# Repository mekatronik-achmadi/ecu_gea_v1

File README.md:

ecu_gea_v1
==========

engine controller unit for gea engines. curently input only RPM and TPS

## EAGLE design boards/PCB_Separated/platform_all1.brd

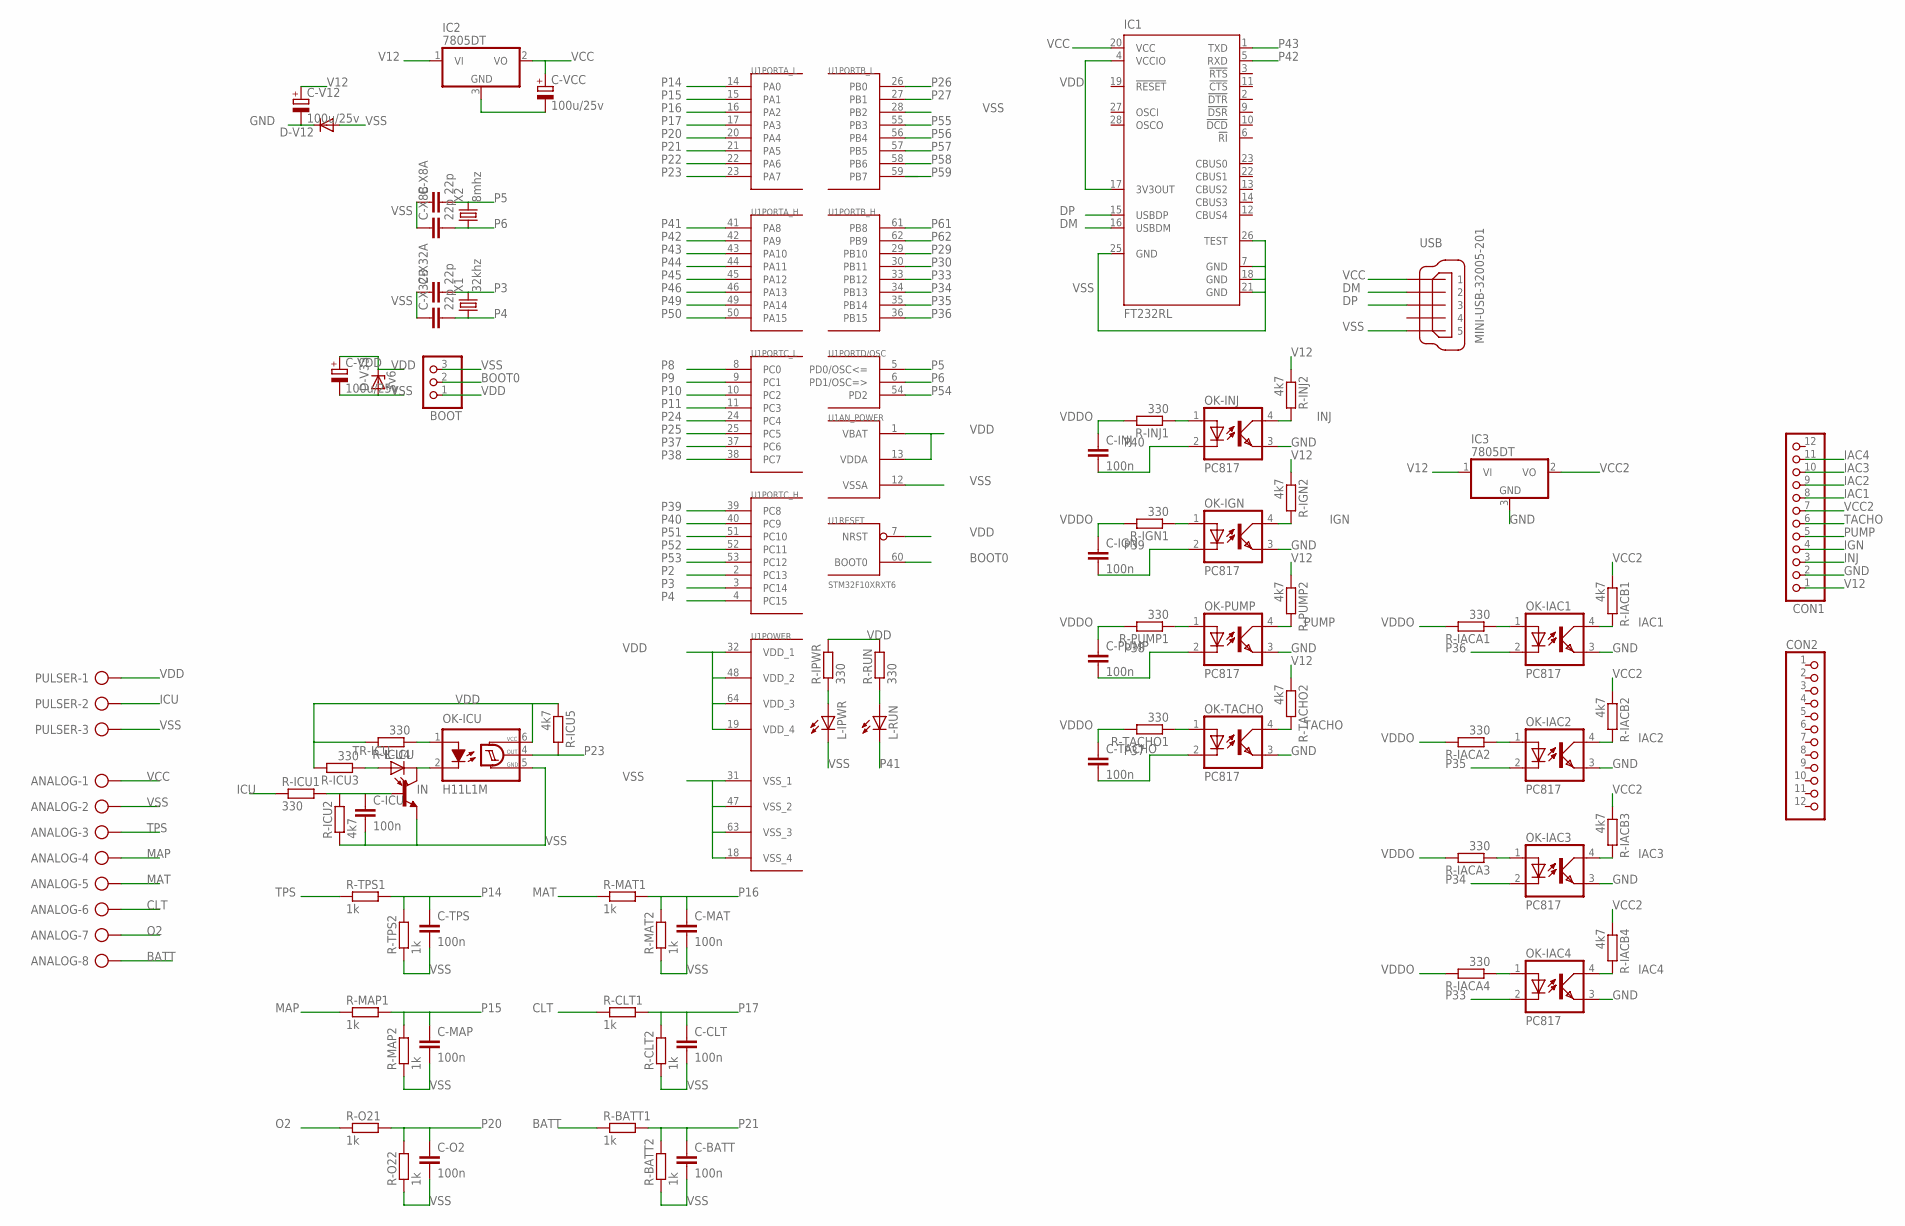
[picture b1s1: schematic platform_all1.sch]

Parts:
ANALOG: AK300/8
BOOT: PINHD-1X3; 1X03
C-BATT: 100n; C1206
C-CLT: 100n; C1206
C-ICU: 100n; C1206
C-IGN: 100n; C1206
C-INJ: 100n; C1206
C-MAP: 100n; C1206
C-MAT: 100n; C1206
C-O2: 100n; C1206
C-PUMP: 100n; C1206
C-TACHO: 100n; C1206
C-TPS: 100n; C1206
C-V12: 100u/25v; PANASONIC_D
C-VCC: 100u/25v; PANASONIC_D
C-VDD: 100u/25v; PANASONIC_D
C-X8A, C-X8B, C-X32A, C-X32B: 22p; C1206
CON1, CON2: PINHD-1X12; 1X12
D-V12: DIODE-SMB; SMB
D-V33: 3v6; SMB
IC1: FT232RL; SSOP28
IC2, IC3: 7805DT; TO252
L-ICU: LEDSMT1206; 1206
L-IPWR: LEDSMT1206; 1206
L-RUN: LEDSMT1206; 1206
OK-IAC1, OK-IAC2, OK-IAC3, OK-IAC4: PC817; DIL04
OK-ICU: H11L1M; DIL06
OK-IGN: PC817; DIL04
OK-INJ: PC817; DIL04
OK-PUMP: PC817; DIL04
OK-TACHO: PC817; DIL04
PULSER: AK300/3
R-BATT1, R-BATT2: 1k; R1206
R-CLT1, R-CLT2: 1k; R1206
R-IACA1, R-IACA2, R-IACA3, R-IACA4: 330; R1206
R-IACB1, R-IACB2, R-IACB3, R-IACB4: 4k7; R1206
R-ICU1, R-ICU3, R-ICU4: 330; R1206
R-ICU2, R-ICU5: 4k7; R1206
R-IGN1: 330; R1206
R-IGN2: 4k7; R1206
R-INJ1: 330; R1206
R-INJ2: 4k7; R1206
R-IPWR: 330; R1206
R-MAP1, R-MAP2: 1k; R1206
R-MAT1, R-MAT2: 1k; R1206
R-O21, R-O22: 1k; R1206
R-PUMP1: 330; R1206
R-PUMP2: 4k7; R1206
R-RUN: 330; R1206
R-TACHO1: 330; R1206
R-TACHO2: 4k7; R1206
R-TPS1, R-TPS2: 1k; R1206
TR-ICU: MMBT3904LT1-NPN-SOT23-BEC; SOT23-BEC
U1: STM32F10XRXT6; TQFP64
USB: MINI-USB-32005-201; 32005-201
X1: 32khz; TC26V
X2: 8mhz; HC49U-V

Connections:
BATT: ANALOG.8, R-BATT1.1
BOOT0: BOOT.2, U1.60 (BOOT0)
CLT: ANALOG.6, R-CLT1.1
DM: IC1.16 (USBDM), USB.2
DP: IC1.15 (USBDP), USB.3
GND: C-V12.-, CON1.2, D-V12.C, IC3.3 (GND), OK-IAC1.3 (EMIT), OK-IAC2.3 (EMIT), OK-IAC3.3 (EMIT), OK-IAC4.3 (EMIT), OK-IGN.3 (EMIT), OK-INJ.3 (EMIT), OK-PUMP.3 (EMIT), OK-TACHO.3 (EMIT)
IAC1: CON1.8, OK-IAC1.4 (COL), R-IACB1.2
IAC2: CON1.9, OK-IAC2.4 (COL), R-IACB2.2
IAC3: CON1.10, OK-IAC3.4 (COL), R-IACB3.2
IAC4: CON1.11, OK-IAC4.4 (COL), R-IACB4.2
ICU: PULSER.2, R-ICU1.1
IGN: CON1.4, OK-IGN.4 (COL), R-IGN2.2
IN: L-ICU.C, OK-ICU.2 (C), TR-ICU.C
INJ: CON1.3, OK-INJ.4 (COL), R-INJ2.2
MAP: ANALOG.4, R-MAP1.1
MAT: ANALOG.5, R-MAT1.1
unnamed: OK-TACHO.1 (A), R-TACHO1.1
unnamed: OK-IAC2.1 (A), R-IACA2.1
unnamed: C-ICU.1, R-ICU1.2, R-ICU2.2, TR-ICU.B
unnamed: OK-IAC1.1 (A), R-IACA1.1
unnamed: OK-ICU.1 (A), R-ICU4.1
unnamed: L-ICU.A, R-ICU3.1
unnamed: L-IPWR.A, R-IPWR.1
unnamed: L-RUN.A, R-RUN.1
unnamed: OK-PUMP.1 (A), R-PUMP1.1
unnamed: OK-IAC3.1 (A), R-IACA3.1
unnamed: OK-IAC4.1 (A), R-IACA4.1
unnamed: OK-INJ.1 (A), R-INJ1.1
unnamed: OK-IGN.1 (A), R-IGN1.1
O2: ANALOG.7, R-O21.1
P2: U1.2 (PC13)
P3: C-X32A.2, U1.3 (PC14), X1.2
P4: C-X32B.2, U1.4 (PC15), X1.1
P5: C-X8A.2, U1.5 (PD0/OSC<=), X2.2
P6: C-X8B.2, U1.6 (PD1/OSC=>), X2.1
P8: U1.8 (PC0)
P9: U1.9 (PC1)
P10: U1.10 (PC2)
P11: U1.11 (PC3)
P14: C-TPS.1, R-TPS1.2, R-TPS2.2, U1.14 (PA0)
P15: C-MAP.1, R-MAP1.2, R-MAP2.2, U1.15 (PA1)
P16: C-MAT.1, R-MAT1.2, R-MAT2.2, U1.16 (PA2)
P17: C-CLT.1, R-CLT1.2, R-CLT2.2, U1.17 (PA3)
P20: C-O2.1, R-O21.2, R-O22.2, U1.20 (PA4)
P21: C-BATT.1, R-BATT1.2, R-BATT2.2, U1.21 (PA5)
P22: U1.22 (PA6)
P23: OK-ICU.4 (OUT), R-ICU5.2, U1.23 (PA7)
P24: U1.24 (PC4)
P25: U1.25 (PC5)
P26: U1.26 (PB0)
P27: U1.27 (PB1)
P29: U1.29 (PB10)
P30: U1.30 (PB11)
P33: OK-IAC4.2 (C), U1.33 (PB12)
P34: OK-IAC3.2 (C), U1.34 (PB13)
P35: OK-IAC2.2 (C), U1.35 (PB14)
P36: OK-IAC1.2 (C), U1.36 (PB15)
P37: C-TACHO.2, OK-TACHO.2 (C), U1.37 (PC6)
P38: C-PUMP.2, OK-PUMP.2 (C), U1.38 (PC7)
P39: C-IGN.2, OK-IGN.2 (C), U1.39 (PC8)
P40: C-INJ.2, OK-INJ.2 (C), U1.40 (PC9)
P41: L-RUN.C, U1.41 (PA8)
P42: IC1.5 (RXD), U1.42 (PA9)
P43: IC1.1 (TXD), U1.43 (PA10)
P44: U1.44 (PA11)
P45: U1.45 (PA12)
P46: U1.46 (PA13)
P49: U1.49 (PA14)
P50: U1.50 (PA15)
P51: U1.51 (PC10)
P52: U1.52 (PC11)
P53: U1.53 (PC12)
P54: U1.54 (PD2)
P55: U1.55 (PB3)
P56: U1.56 (PB4)
P57: U1.57 (PB5)
P58: U1.58 (PB6)
P59: U1.59 (PB7)
P61: U1.61 (PB8)
P62: U1.62 (PB9)
PUMP: CON1.5, OK-PUMP.4 (COL), R-PUMP2.2
TACHO: CON1.6, OK-TACHO.4 (COL), R-TACHO2.2
TPS: ANALOG.3, R-TPS1.1
V12: C-V12.+, CON1.1, IC2.1 (VI), IC3.1 (VI), R-IGN2.1, R-INJ2.1, R-PUMP2.1, R-TACHO2.1
VCC: ANALOG.1, C-VCC.+, IC1.20 (VCC), IC2.2 (VO), USB.1
VCC2: CON1.7, IC3.2 (VO), R-IACB1.1, R-IACB2.1, R-IACB3.1, R-IACB4.1
VDD: BOOT.1, C-VDD.+, D-V33.C, IC1.4 (VCCIO), IC1.17 (3V3OUT), OK-ICU.6 (VCC), PULSER.1, R-ICU3.2, R-ICU4.2, R-ICU5.1, R-IPWR.2, R-RUN.2, U1.1 (VBAT), U1.7 (NRST), U1.13 (VDDA), U1.19 (VDD_4), U1.32 (VDD_1), U1.48 (VDD_2), U1.64 (VDD_3)
VDDO: C-IGN.1, C-INJ.1, C-PUMP.1, C-TACHO.1, R-IACA1.2, R-IACA2.2, R-IACA3.2, R-IACA4.2, R-IGN1.2, R-INJ1.2, R-PUMP1.2, R-TACHO1.2
VSS: ANALOG.2, BOOT.3, C-BATT.2, C-CLT.2, C-ICU.2, C-MAP.2, C-MAT.2, C-O2.2, C-TPS.2, C-VCC.-, C-VDD.-, C-X8A.1, C-X8B.1, C-X32A.1, C-X32B.1, D-V12.A, D-V33.A, IC1.7 (GND), IC1.18 (GND), IC1.21 (GND), IC1.25 (GND), IC1.26 (TEST), IC2.3 (GND), L-IPWR.C, OK-ICU.5 (GND), PULSER.3, R-BATT2.1, R-CLT2.1, R-ICU2.1, R-MAP2.1, R-MAT2.1, R-O22.1, R-TPS2.1, TR-ICU.E, U1.12 (VSSA), U1.18 (VSS_4), U1.28 (PB2), U1.31 (VSS_1), U1.47 (VSS_2), U1.63 (VSS_3), USB.5

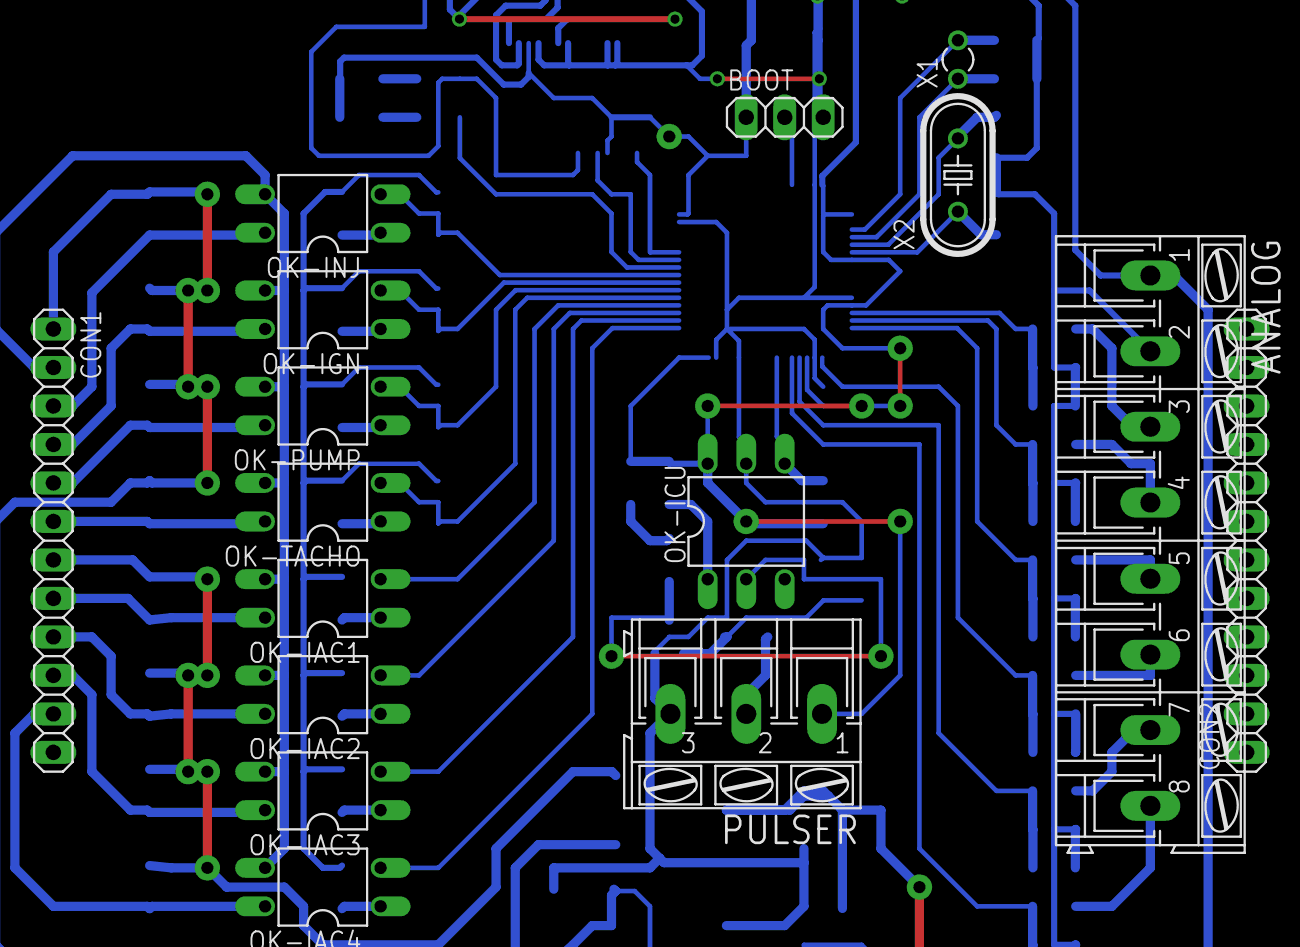
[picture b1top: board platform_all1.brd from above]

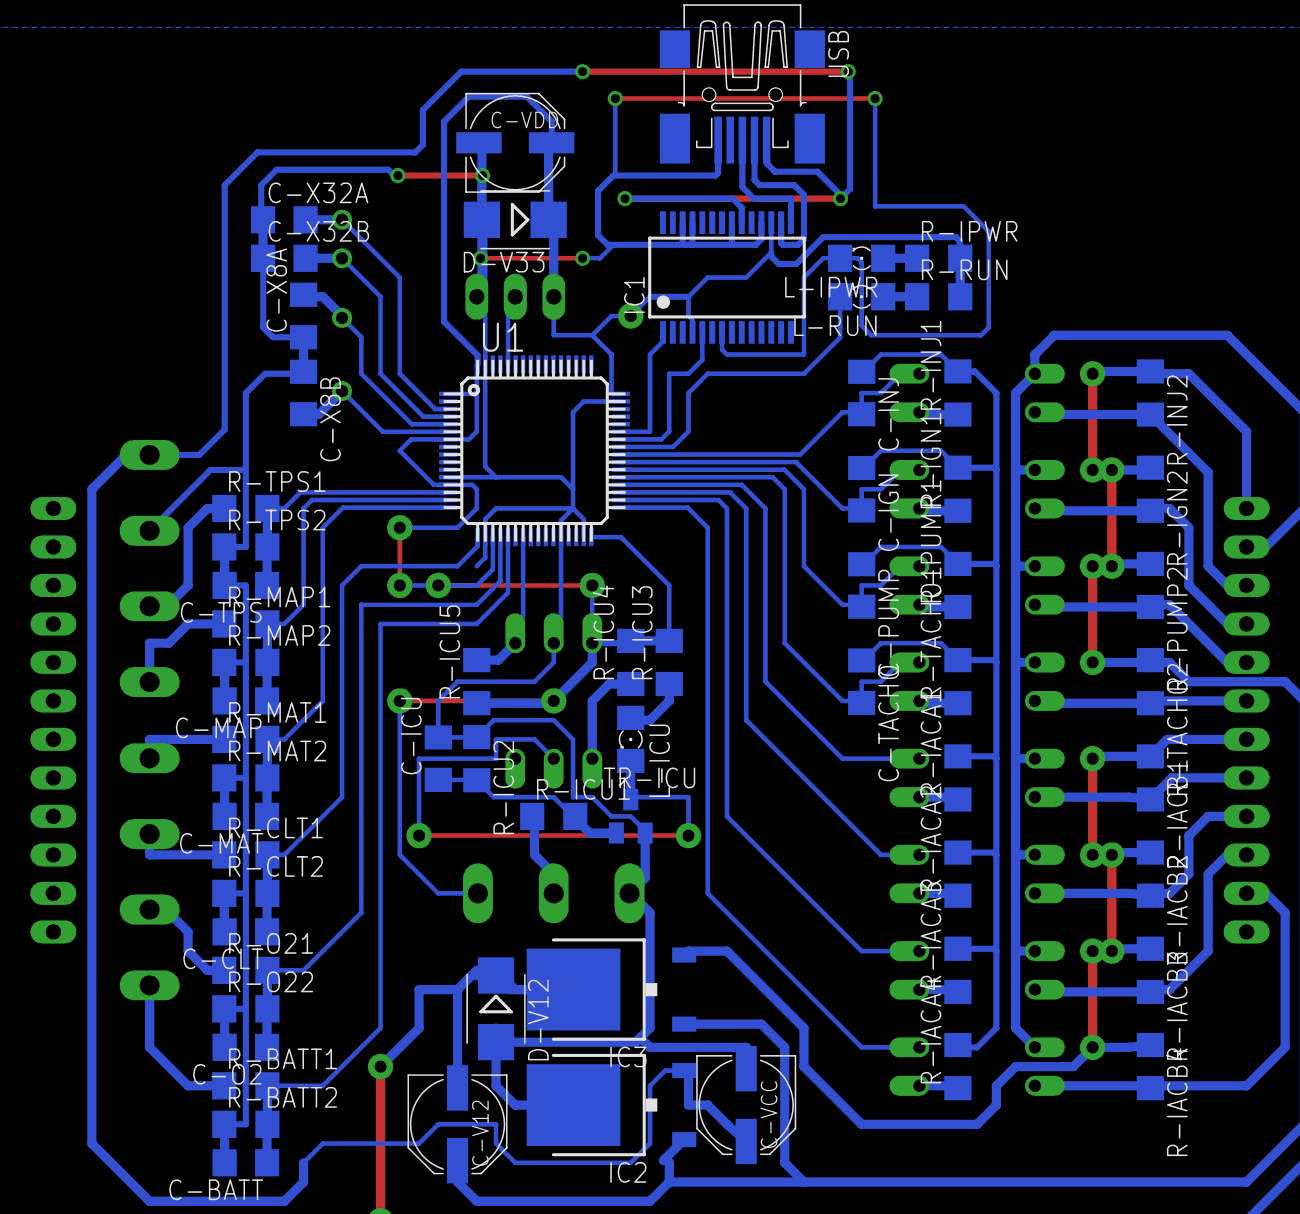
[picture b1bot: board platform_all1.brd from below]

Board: 2 copper layers, 80 parts (64 on the bottom side), 61 nets.

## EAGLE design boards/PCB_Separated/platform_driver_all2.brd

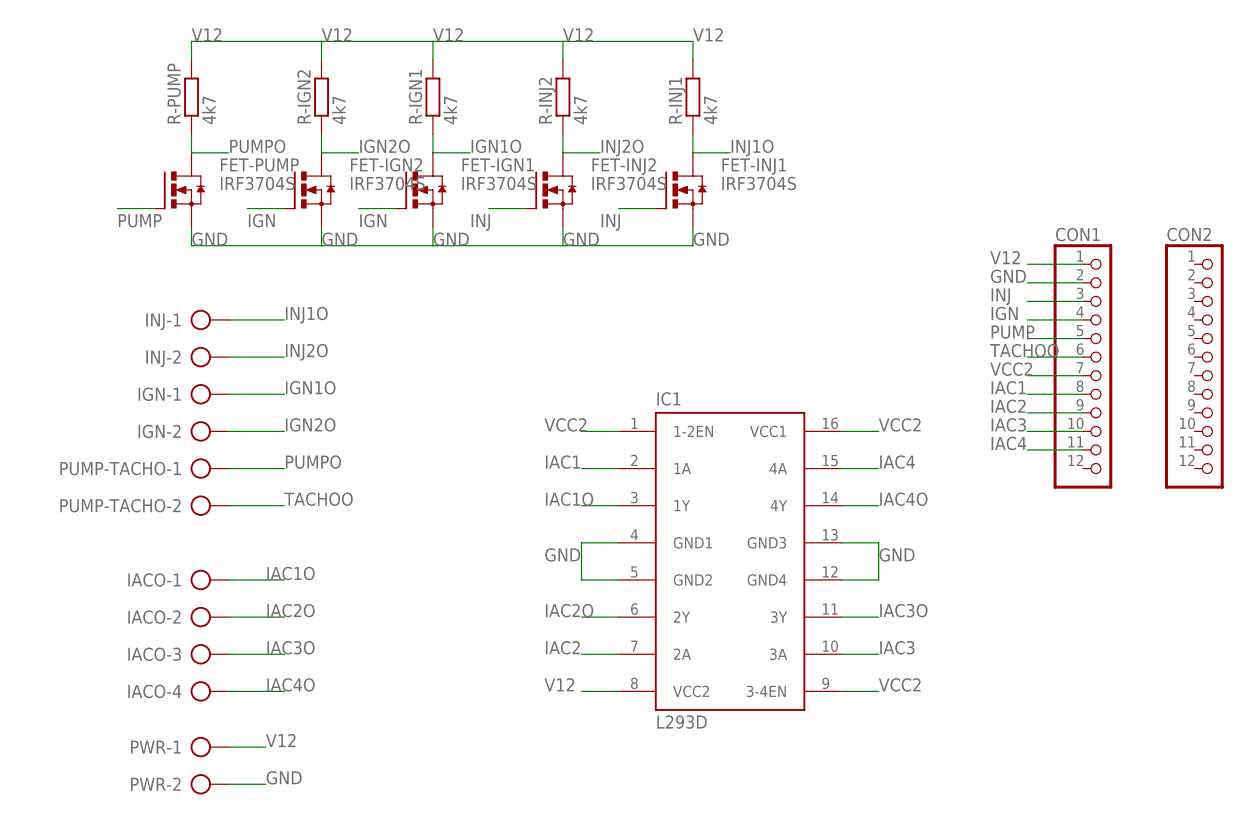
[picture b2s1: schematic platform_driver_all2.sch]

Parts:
CON1, CON2: PINHD-1X12; 1X12
FET-IGN1, FET-IGN2: IRF3704S; D2PACK
FET-INJ1, FET-INJ2: IRF3704S; D2PACK
FET-PUMP: IRF3704S; D2PACK
IACO: AK300/4
IC1: L293D; DIL16
IGN: AK300/2
INJ: AK300/2
PUMP-TACHO: AK300/2
PWR: AK300/2
R-IGN1, R-IGN2: 4k7; M1206
R-INJ1, R-INJ2: 4k7; M1206
R-PUMP: 4k7; M1206

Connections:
GND: CON1.2, FET-IGN1.3 (S), FET-IGN2.3 (S), FET-INJ1.3 (S), FET-INJ2.3 (S), FET-PUMP.3 (S), IC1.4 (GND1), IC1.5 (GND2), IC1.12 (GND4), IC1.13 (GND3), PWR.2
IAC1: CON1.8, IC1.2 (1A)
IAC1O: IACO.1, IC1.3 (1Y)
IAC2: CON1.9, IC1.7 (2A)
IAC2O: IACO.2, IC1.6 (2Y)
IAC3: CON1.10, IC1.10 (3A)
IAC3O: IACO.3, IC1.11 (3Y)
IAC4: CON1.11, IC1.15 (4A)
IAC4O: IACO.4, IC1.14 (4Y)
IGN: CON1.4, FET-IGN1.1 (G), FET-IGN2.1 (G)
IGN1O: FET-IGN1.2 (D), IGN.1, R-IGN1.1
IGN2O: FET-IGN2.2 (D), IGN.2, R-IGN2.1
INJ: CON1.3, FET-INJ1.1 (G), FET-INJ2.1 (G)
INJ1O: FET-INJ1.2 (D), INJ.1, R-INJ1.1
INJ2O: FET-INJ2.2 (D), INJ.2, R-INJ2.1
PUMP: CON1.5, FET-PUMP.1 (G)
PUMPO: FET-PUMP.2 (D), PUMP-TACHO.1, R-PUMP.1
TACHOO: CON1.6, PUMP-TACHO.2
V12: CON1.1, IC1.8 (VCC2), PWR.1, R-IGN1.2, R-IGN2.2, R-INJ1.2, R-INJ2.2, R-PUMP.2
VCC2: CON1.7, IC1.1 (1-2EN), IC1.9 (3-4EN), IC1.16 (VCC1)

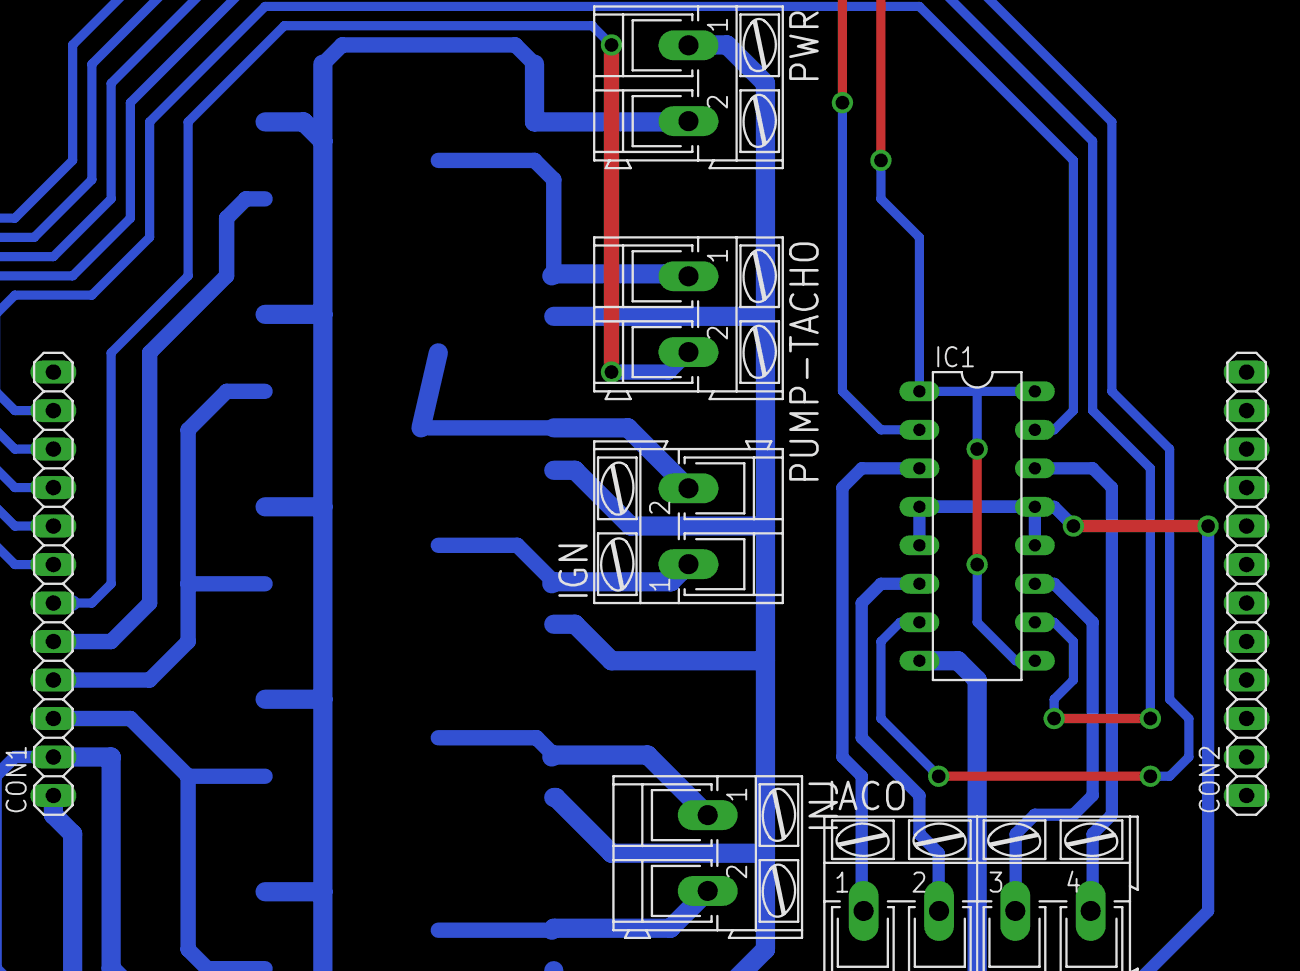
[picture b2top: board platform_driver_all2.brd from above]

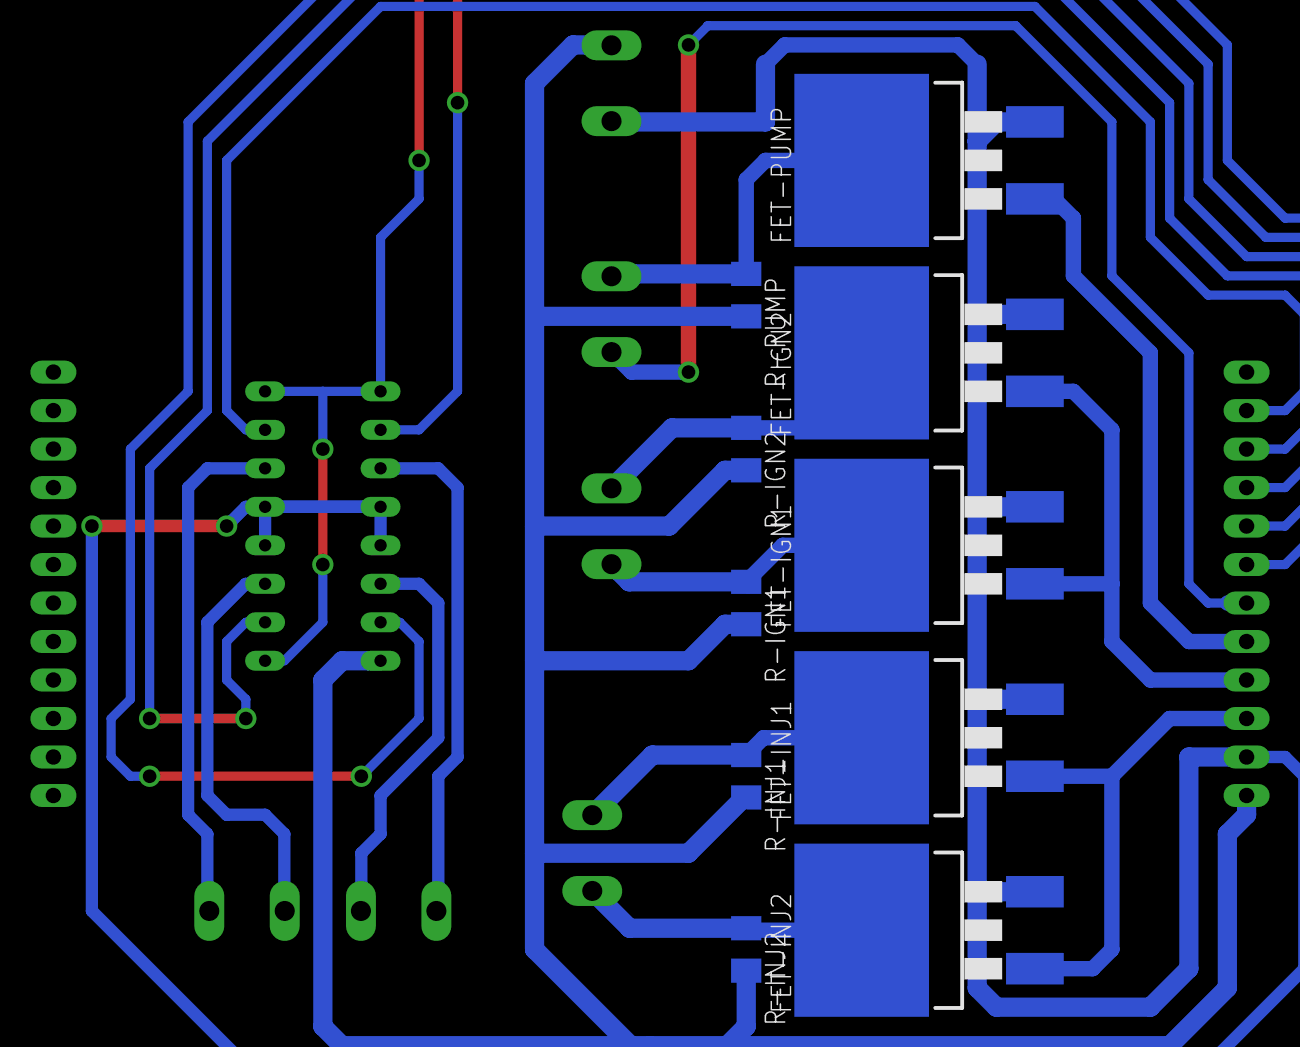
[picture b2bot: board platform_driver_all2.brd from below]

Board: 2 copper layers, 18 parts (10 on the bottom side), 20 nets.

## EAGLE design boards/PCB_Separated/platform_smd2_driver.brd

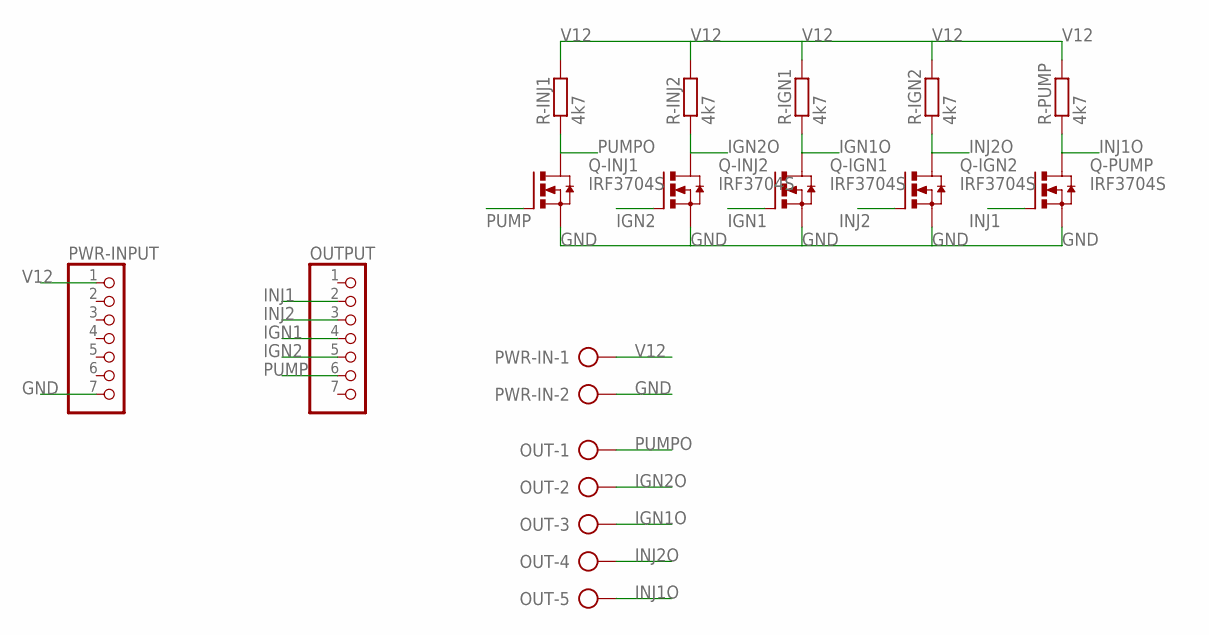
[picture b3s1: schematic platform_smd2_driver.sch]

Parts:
OUT: AK300/5
OUTPUT: PINHD-1X7; 1X07
PWR-IN: AK300/2
PWR-INPUT: PINHD-1X7; 1X07
Q-IGN1, Q-IGN2: IRF3704S; D2PACK
Q-INJ1, Q-INJ2: IRF3704S; D2PACK
Q-PUMP: IRF3704S; D2PACK
R-IGN1, R-IGN2: 4k7; M1206
R-INJ1, R-INJ2: 4k7; M1206
R-PUMP: 4k7; M1206

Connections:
GND: PWR-IN.2, PWR-INPUT.7, Q-IGN1.3 (S), Q-IGN2.3 (S), Q-INJ1.3 (S), Q-INJ2.3 (S), Q-PUMP.3 (S)
IGN1: OUTPUT.4, Q-IGN1.1 (G)
IGN1O: OUT.3, Q-IGN1.2 (D), R-IGN1.1
IGN2: OUTPUT.5, Q-INJ2.1 (G)
IGN2O: OUT.2, Q-INJ2.2 (D), R-INJ2.1
INJ1: OUTPUT.2, Q-PUMP.1 (G)
INJ1O: OUT.5, Q-PUMP.2 (D), R-PUMP.1
INJ2: OUTPUT.3, Q-IGN2.1 (G)
INJ2O: OUT.4, Q-IGN2.2 (D), R-IGN2.1
PUMP: OUTPUT.6, Q-INJ1.1 (G)
PUMPO: OUT.1, Q-INJ1.2 (D), R-INJ1.1
V12: PWR-IN.1, PWR-INPUT.1, R-IGN1.2, R-IGN2.2, R-INJ1.2, R-INJ2.2, R-PUMP.2

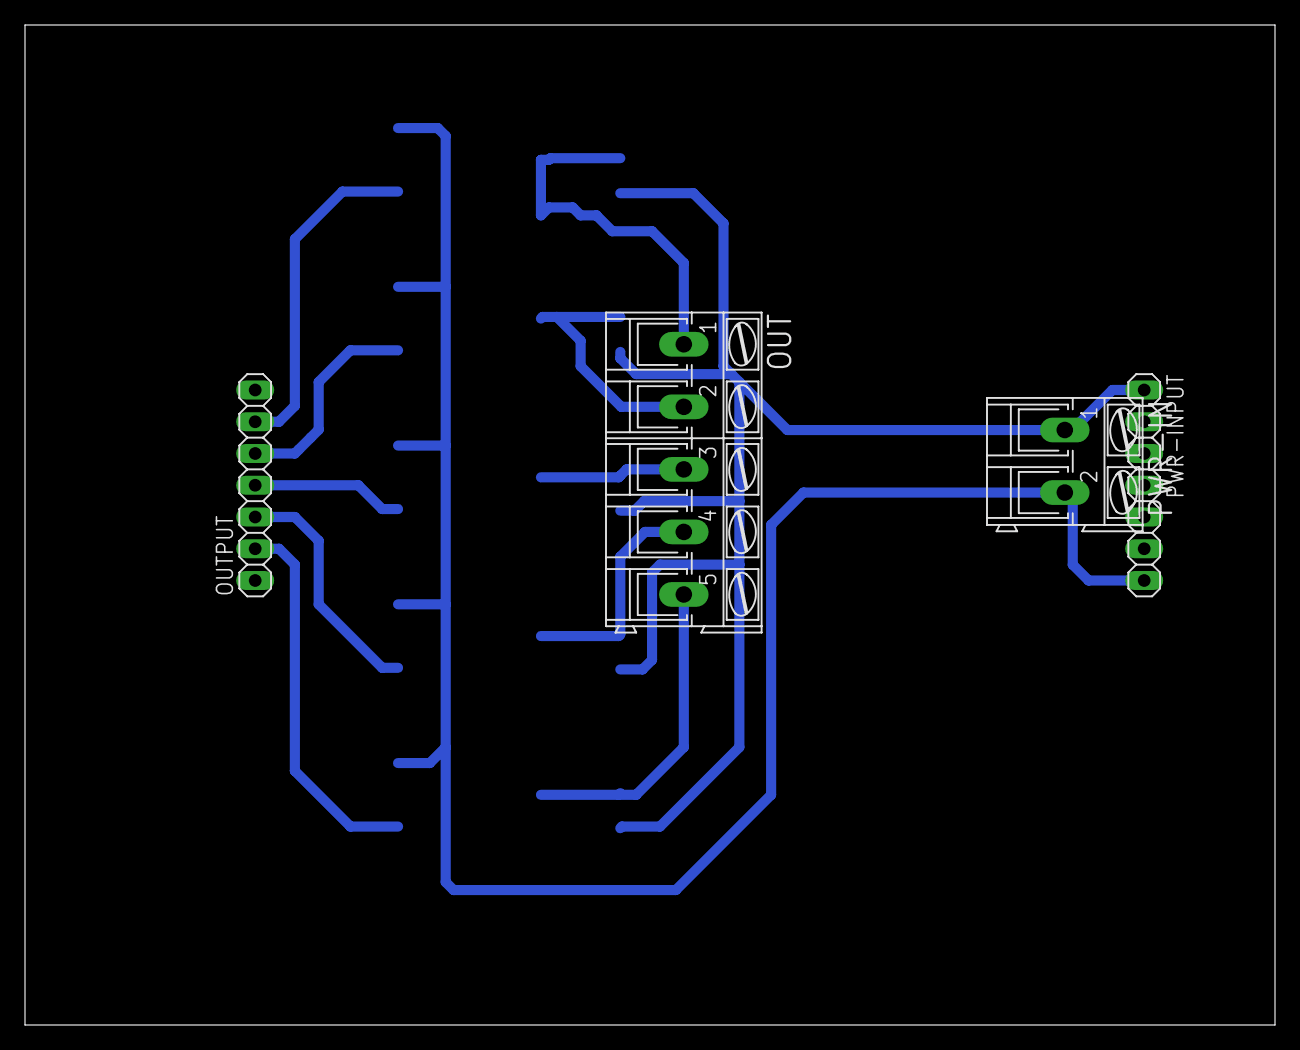
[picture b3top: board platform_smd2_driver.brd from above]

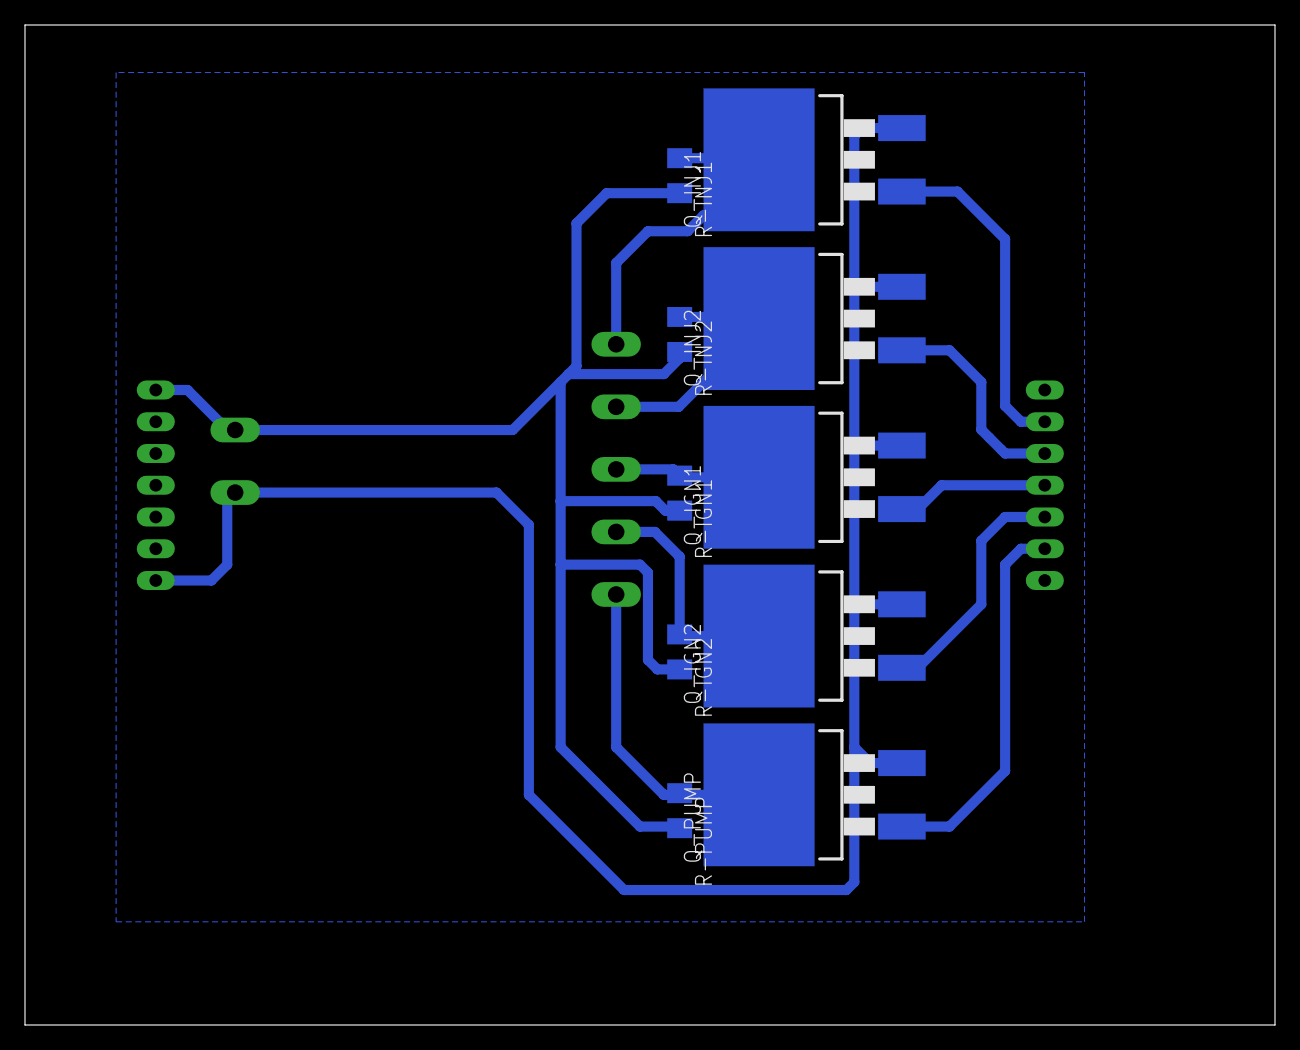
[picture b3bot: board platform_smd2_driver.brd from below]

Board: 2 copper layers, 100.0 x 80.0 mm, 14 parts (10 on the bottom side), 12 nets.

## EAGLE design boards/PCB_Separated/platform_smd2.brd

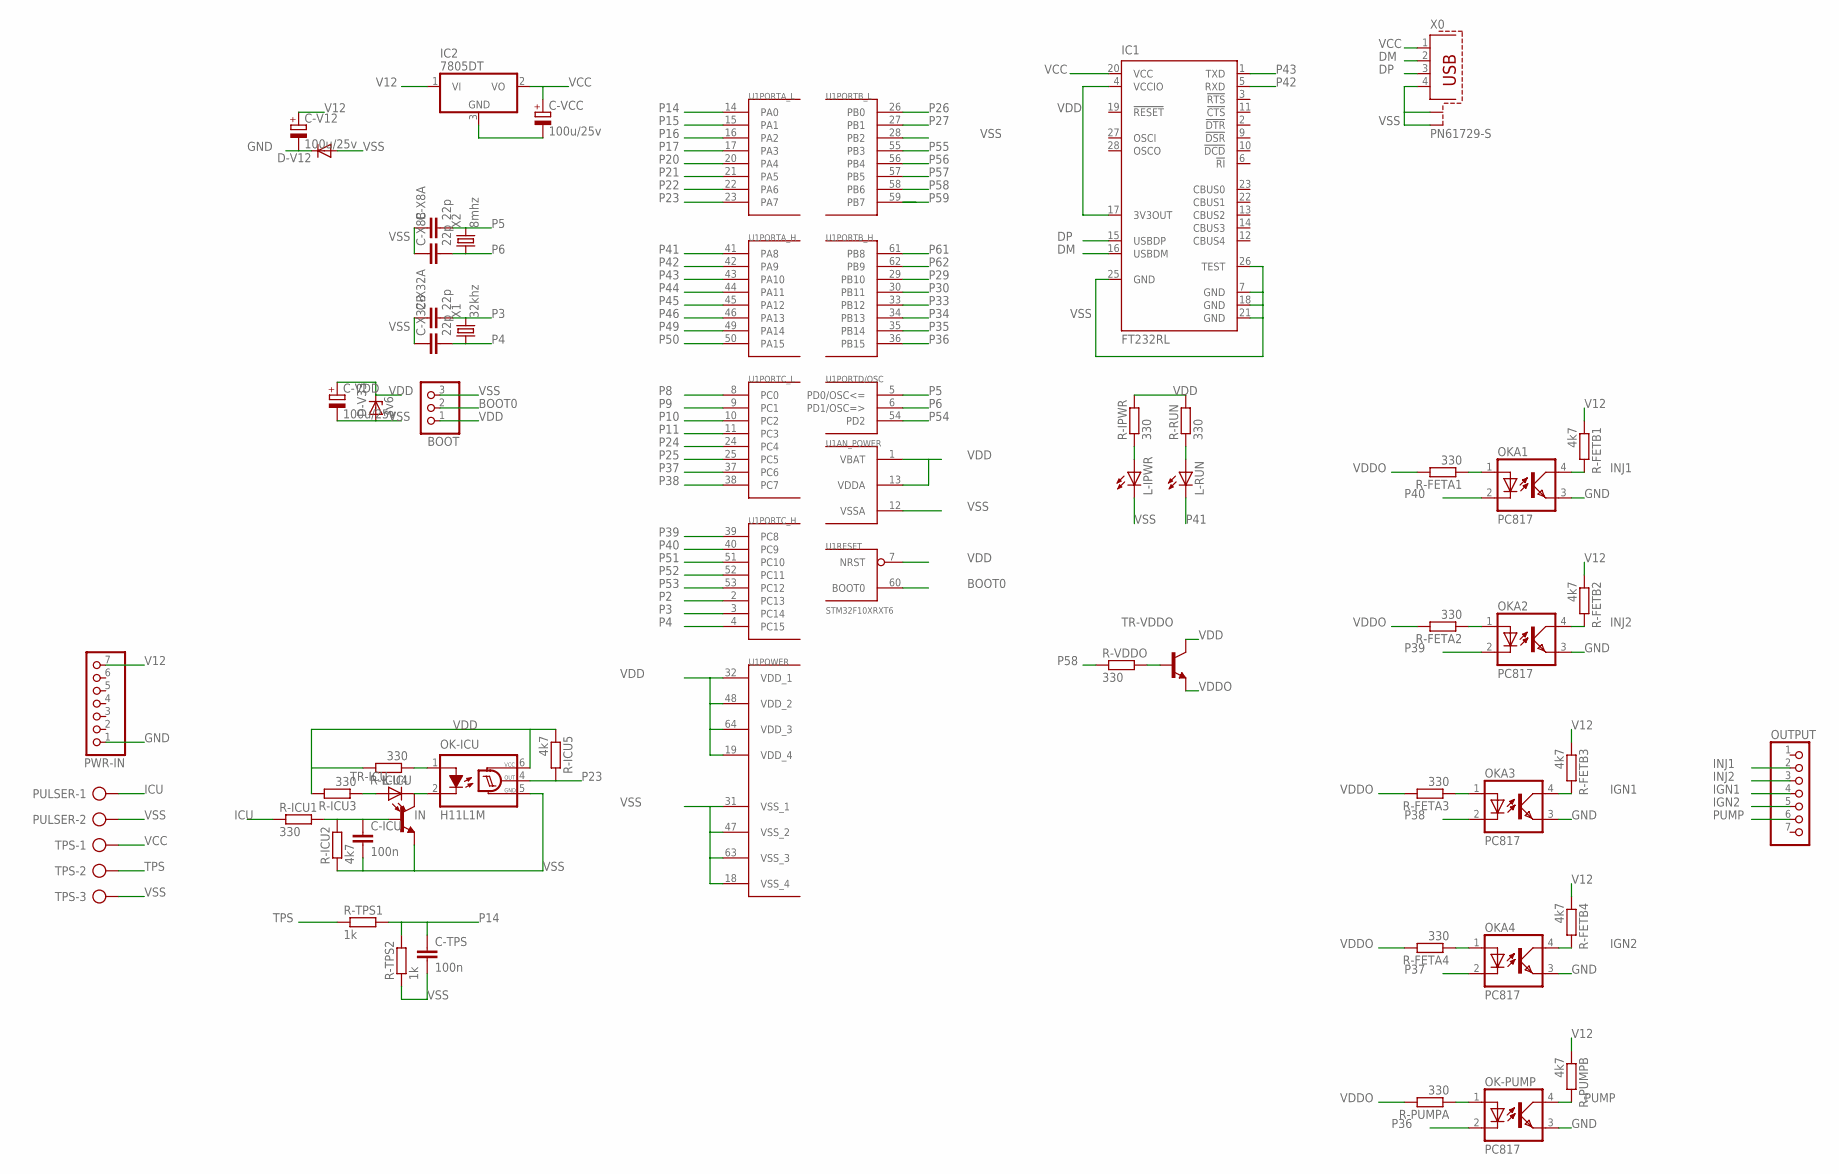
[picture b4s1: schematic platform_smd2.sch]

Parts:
BOOT: PINHD-1X3; 1X03
C-ICU: 100n; C1206
C-TPS: 100n; C1206
C-V12: 100u/25v; PANASONIC_D
C-VCC: 100u/25v; PANASONIC_D
C-VDD: 100u/25v; PANASONIC_D
C-X8A, C-X8B, C-X32A, C-X32B: 22p; C1206
D-V12: DIODE-SMB; SMB
D-V33: 3v6; SMB
IC1: FT232RL; SSOP28
IC2: 7805DT; TO252
L-ICU: LEDSML0805; SML0805
L-IPWR: LEDSMT1206; 1206
L-RUN: LEDSMT1206; 1206
OK-ICU: H11L1M; DIL06
OK-PUMP: PC817; DIL04
OKA1, OKA2, OKA3, OKA4: PC817; DIL04
OUTPUT: PINHD-1X7; 1X07
PULSER: AK300/2
PWR-IN: PINHD-1X7; 1X07
R-FETA1, R-FETA2, R-FETA3, R-FETA4: 330; R1206
R-FETB1, R-FETB2, R-FETB3, R-FETB4: 4k7; R1206
R-ICU1, R-ICU3, R-ICU4: 330; R1206
R-ICU2, R-ICU5: 4k7; R1206
R-IPWR: 330; R1206
R-PUMPA: 330; R1206
R-PUMPB: 4k7; R1206
R-RUN: 330; R1206
R-TPS1, R-TPS2: 1k; R1206
R-VDDO: 330; R0805
TPS: AK300/3
TR-ICU: MMBT3904LT1-NPN-SOT23-BEC; SOT23-BEC
TR-VDDO: MMBT3904LT1-NPN-SOT23-BEC; SOT23-BEC
U1: STM32F10XRXT6; TQFP64
X0: PN61729-S
X1: 32khz; TC26V
X2: 8mhz; HC49U-V

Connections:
BOOT0: BOOT.2, U1.60 (BOOT0)
DM: IC1.16 (USBDM), X0.2
DP: IC1.15 (USBDP), X0.3
GND: C-V12.-, D-V12.C, OK-PUMP.3 (EMIT), OKA1.3 (EMIT), OKA2.3 (EMIT), OKA3.3 (EMIT), OKA4.3 (EMIT), PWR-IN.1
ICU: PULSER.1, R-ICU1.1
IGN1: OKA3.4 (COL), OUTPUT.4, R-FETB3.2
IGN2: OKA4.4 (COL), OUTPUT.5, R-FETB4.2
IN: L-ICU.C, OK-ICU.2 (C), TR-ICU.C
INJ1: OKA1.4 (COL), OUTPUT.2, R-FETB1.2
INJ2: OKA2.4 (COL), OUTPUT.3, R-FETB2.2
unnamed: C-ICU.1, R-ICU1.2, R-ICU2.2, TR-ICU.B
unnamed: OK-ICU.1 (A), R-ICU4.1
unnamed: L-ICU.A, R-ICU3.1
unnamed: L-IPWR.A, R-IPWR.1
unnamed: L-RUN.A, R-RUN.1
unnamed: OK-PUMP.1 (A), R-PUMPA.1
unnamed: OKA2.1 (A), R-FETA2.1
unnamed: OKA1.1 (A), R-FETA1.1
unnamed: OKA3.1 (A), R-FETA3.1
unnamed: OKA4.1 (A), R-FETA4.1
unnamed: R-VDDO.2, TR-VDDO.B
P2: U1.2 (PC13)
P3: C-X32A.2, U1.3 (PC14), X1.2
P4: C-X32B.2, U1.4 (PC15), X1.1
P5: C-X8A.2, U1.5 (PD0/OSC<=), X2.2
P6: C-X8B.2, U1.6 (PD1/OSC=>), X2.1
P8: U1.8 (PC0)
P9: U1.9 (PC1)
P10: U1.10 (PC2)
P11: U1.11 (PC3)
P14: C-TPS.1, R-TPS1.2, R-TPS2.2, U1.14 (PA0)
P15: U1.15 (PA1)
P16: U1.16 (PA2)
P17: U1.17 (PA3)
P20: U1.20 (PA4)
P21: U1.21 (PA5)
P22: U1.22 (PA6)
P23: OK-ICU.4 (OUT), R-ICU5.2, U1.23 (PA7)
P24: U1.24 (PC4)
P25: U1.25 (PC5)
P26: U1.26 (PB0)
P27: U1.27 (PB1)
P29: U1.29 (PB10)
P30: U1.30 (PB11)
P33: U1.33 (PB12)
P34: U1.34 (PB13)
P35: U1.35 (PB14)
P36: OK-PUMP.2 (C), U1.36 (PB15)
P37: OKA4.2 (C), U1.37 (PC6)
P38: OKA3.2 (C), U1.38 (PC7)
P39: OKA2.2 (C), U1.39 (PC8)
P40: OKA1.2 (C), U1.40 (PC9)
P41: L-RUN.C, U1.41 (PA8)
P42: IC1.5 (RXD), U1.42 (PA9)
P43: IC1.1 (TXD), U1.43 (PA10)
P44: U1.44 (PA11)
P45: U1.45 (PA12)
P46: U1.46 (PA13)
P49: U1.49 (PA14)
P50: U1.50 (PA15)
P51: U1.51 (PC10)
P52: U1.52 (PC11)
P53: U1.53 (PC12)
P54: U1.54 (PD2)
P55: U1.55 (PB3)
P56: U1.56 (PB4)
P57: U1.57 (PB5)
P58: R-VDDO.1, U1.58 (PB6)
P59: U1.59 (PB7)
P61: U1.61 (PB8)
P62: U1.62 (PB9)
PUMP: OK-PUMP.4 (COL), OUTPUT.6, R-PUMPB.2
TPS: R-TPS1.1, TPS.2
V12: C-V12.+, IC2.1 (VI), PWR-IN.7, R-FETB1.1, R-FETB2.1, R-FETB3.1, R-FETB4.1, R-PUMPB.1
VCC: C-VCC.+, IC1.20 (VCC), IC2.2 (VO), TPS.1, X0.1
VDD: BOOT.1, C-VDD.+, D-V33.C, IC1.4 (VCCIO), IC1.17 (3V3OUT), OK-ICU.6 (VCC), R-ICU3.2, R-ICU4.2, R-ICU5.1, R-IPWR.2, R-RUN.2, TR-VDDO.C, U1.1 (VBAT), U1.7 (NRST), U1.13 (VDDA), U1.19 (VDD_4), U1.32 (VDD_1), U1.48 (VDD_2), U1.64 (VDD_3)
VDDO: R-FETA1.2, R-FETA2.2, R-FETA3.2, R-FETA4.2, R-PUMPA.2, TR-VDDO.E
VSS: BOOT.3, C-ICU.2, C-TPS.2, C-VCC.-, C-VDD.-, C-X8A.1, C-X8B.1, C-X32A.1, C-X32B.1, D-V12.A, D-V33.A, IC1.7 (GND), IC1.18 (GND), IC1.21 (GND), IC1.25 (GND), IC1.26 (TEST), IC2.3 (GND), L-IPWR.C, OK-ICU.5 (GND), PULSER.2, R-ICU2.1, R-TPS2.1, TPS.3, TR-ICU.E, U1.12 (VSSA), U1.18 (VSS_4), U1.28 (PB2), U1.31 (VSS_1), U1.47 (VSS_2), U1.63 (VSS_3), X0.4, X0.S1, X0.S2
